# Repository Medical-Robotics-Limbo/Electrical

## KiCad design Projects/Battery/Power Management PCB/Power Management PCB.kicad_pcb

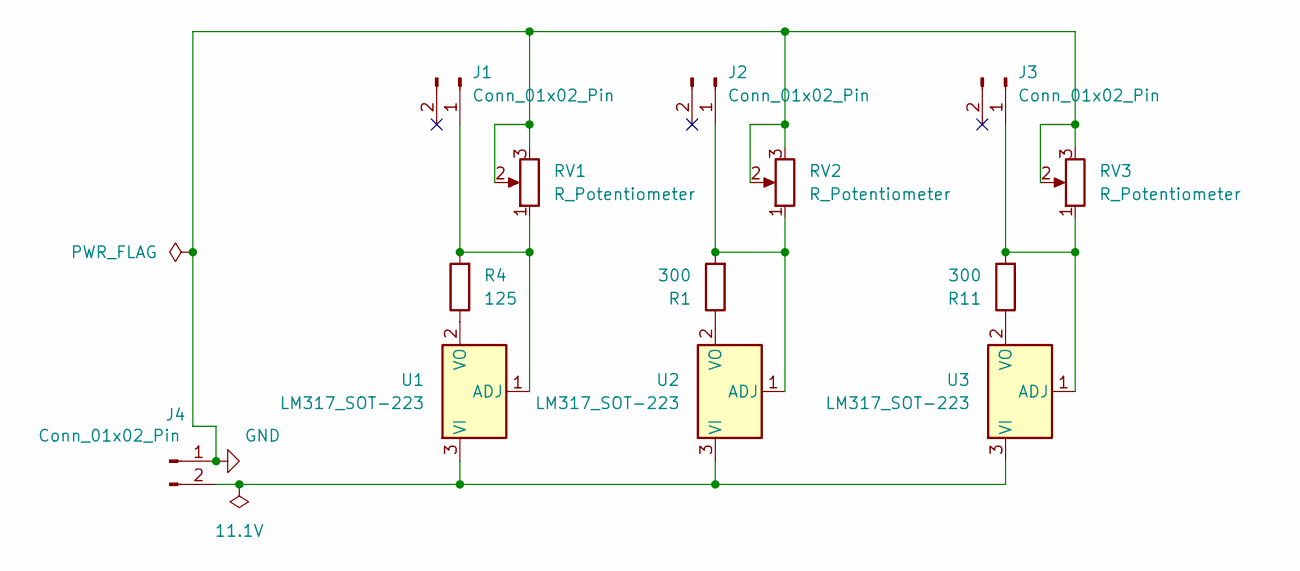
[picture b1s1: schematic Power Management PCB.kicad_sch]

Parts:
J1, J2, J3, J4: Conn_01x02_Pin; PinHeader_1x02_P1.27mm_Vertical_SMD_Pin1Left
R1, R11: 300; R_0201_0603Metric
R4: 125; R_0201_0603Metric
RV1, RV2, RV3: R_Potentiometer; Potentiometer_Bourns_3314J_Vertical
U1, U2, U3: LM317_SOT-223; SOT-223-3_TabPin2

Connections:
GND: J4.1, RV1.2, RV1.3, RV2.2, RV2.3, RV3.2, RV3.3
unnamed: J1.1, R4.2, RV1.1, U1.1 (ADJ)
unnamed: J2.1, R1.2, RV2.1, U2.1 (ADJ)
unnamed: J3.1, R11.2, RV3.1, U3.1 (ADJ)
unnamed: J4.2, U1.3 (VI), U2.3 (VI), U3.3 (VI)
unnamed: R4.1, U1.2 (VO)
unnamed: R1.1, U2.2 (VO)
unnamed: R11.1, U3.2 (VO)

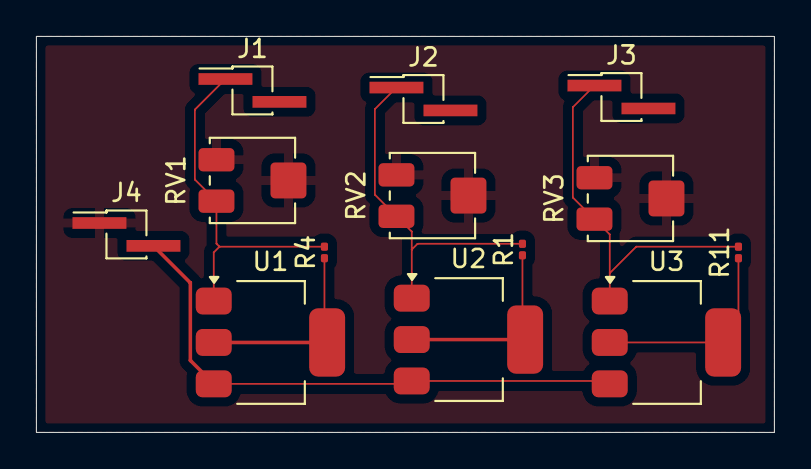
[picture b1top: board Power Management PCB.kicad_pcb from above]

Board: 2 copper layers, 41.0 x 22.0 mm, 13 parts (0 on the bottom side), 8 nets.

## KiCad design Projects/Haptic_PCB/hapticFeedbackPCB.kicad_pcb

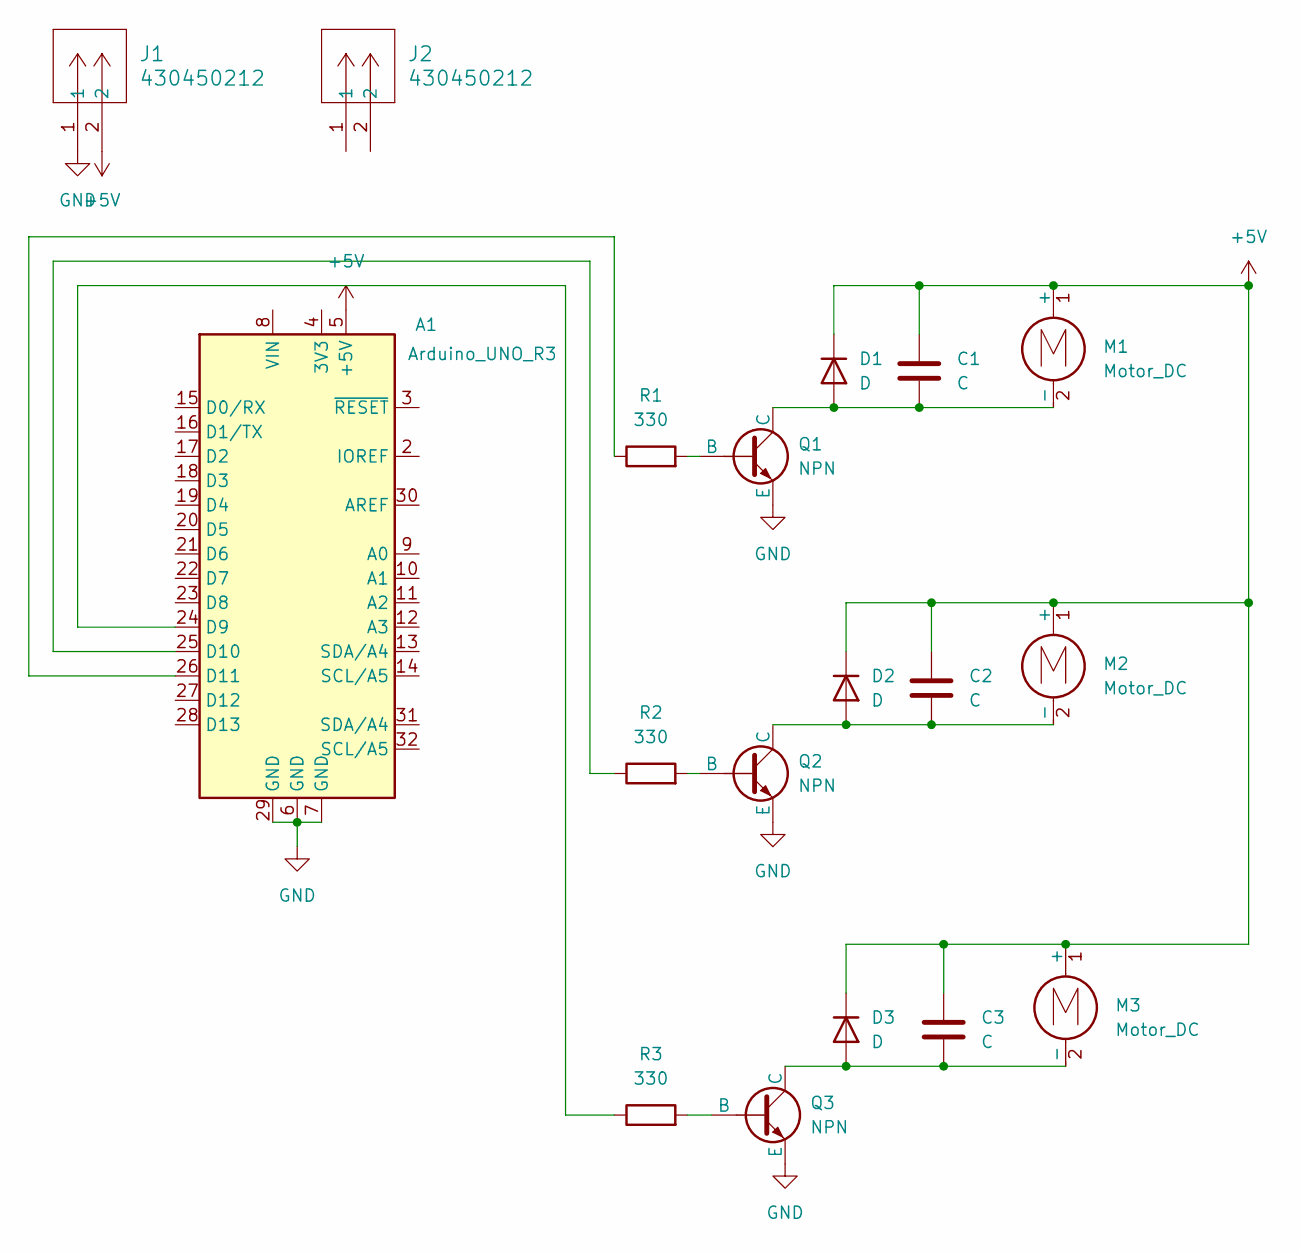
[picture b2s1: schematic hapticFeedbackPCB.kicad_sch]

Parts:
A1: Arduino_UNO_R3
C1, C2, C3: C; CP_Radial_D8.0mm_P5.00mm
D1, D2, D3: D; D_5W_P10.16mm_Horizontal
J1, J2: 430450212; CON_430450212_MOL
M1, M2, M3: Motor_DC; CON_430450212_MOL
Q1, Q2, Q3: NPN; TO-18_TO-206AA_5P8_ONS
R1, R2, R3: 330; R_Axial_DIN0207_L6.3mm_D2.5mm_P10.16mm_Horizontal

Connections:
+5V: A1.5 (+5V), C1.1, C2.1, C3.1, D1.1 (K), D2.1 (K), D3.1 (K), J1.2, M1.1 (+), M2.1 (+), M3.1 (+)
GND: A1.6 (GND), A1.7 (GND), A1.29 (GND), J1.1, Q1.3 (E), Q2.3 (E), Q3.3 (E)
unnamed: A1.24 (D9), R3.1
unnamed: A1.25 (D10), R2.1
unnamed: A1.26 (D11), R1.1
unnamed: C1.2, D1.2 (A), M1.2 (-), Q1.1 (C)
unnamed: C2.2, D2.2 (A), M2.2 (-), Q2.1 (C)
unnamed: C3.2, D3.2 (A), M3.2 (-), Q3.1 (C)
unnamed: Q1.2 (B), R1.2
unnamed: Q2.2 (B), R2.2
unnamed: Q3.2 (B), R3.2

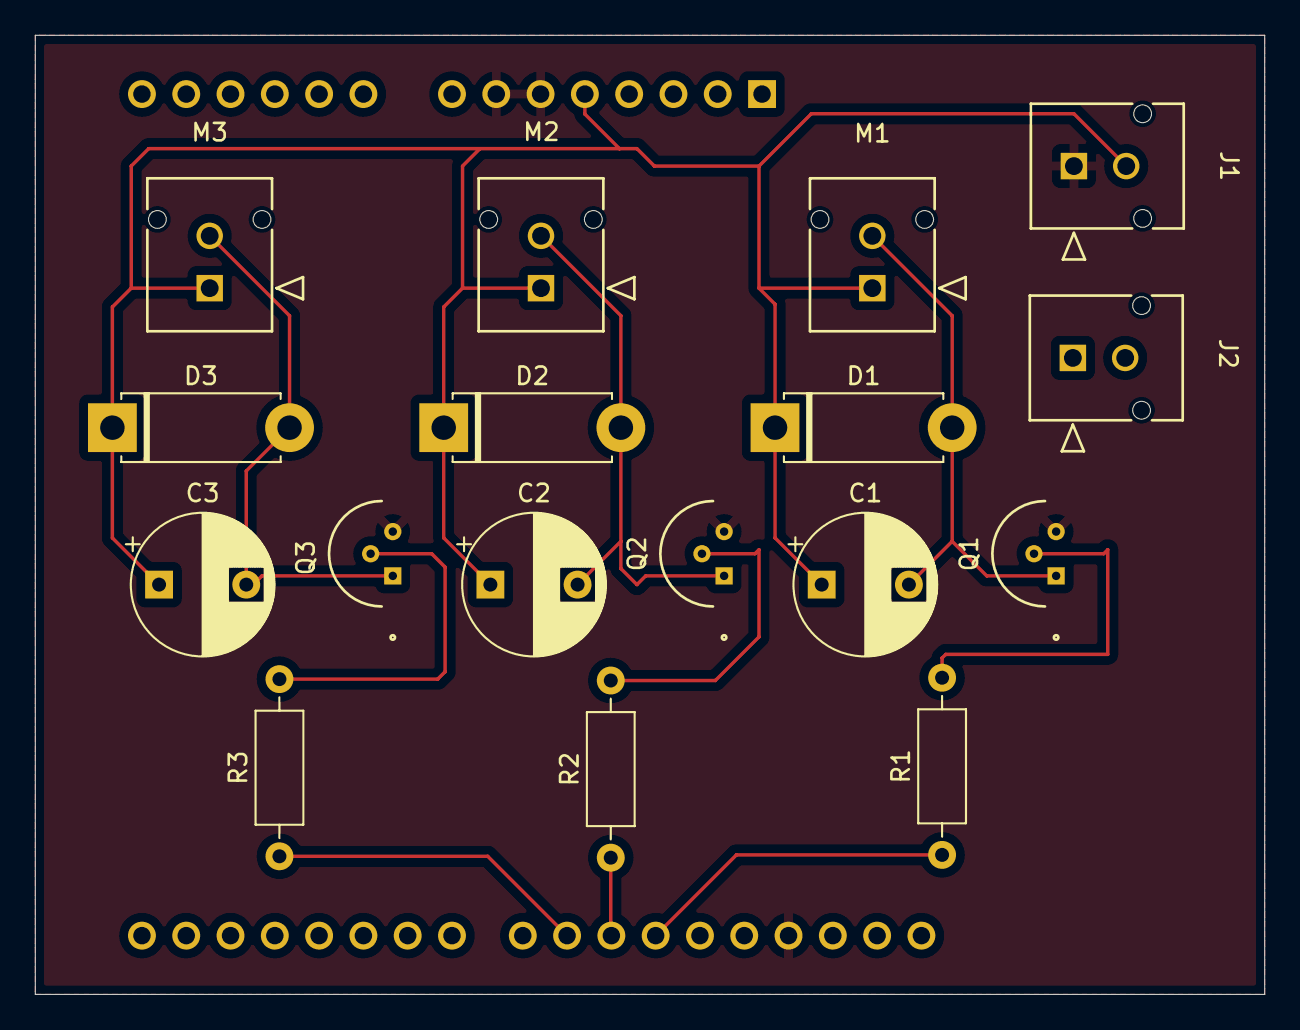
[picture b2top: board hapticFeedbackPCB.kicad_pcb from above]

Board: 2 copper layers, 70.5 x 55.0 mm, 18 parts (1 on the bottom side), 11 nets.

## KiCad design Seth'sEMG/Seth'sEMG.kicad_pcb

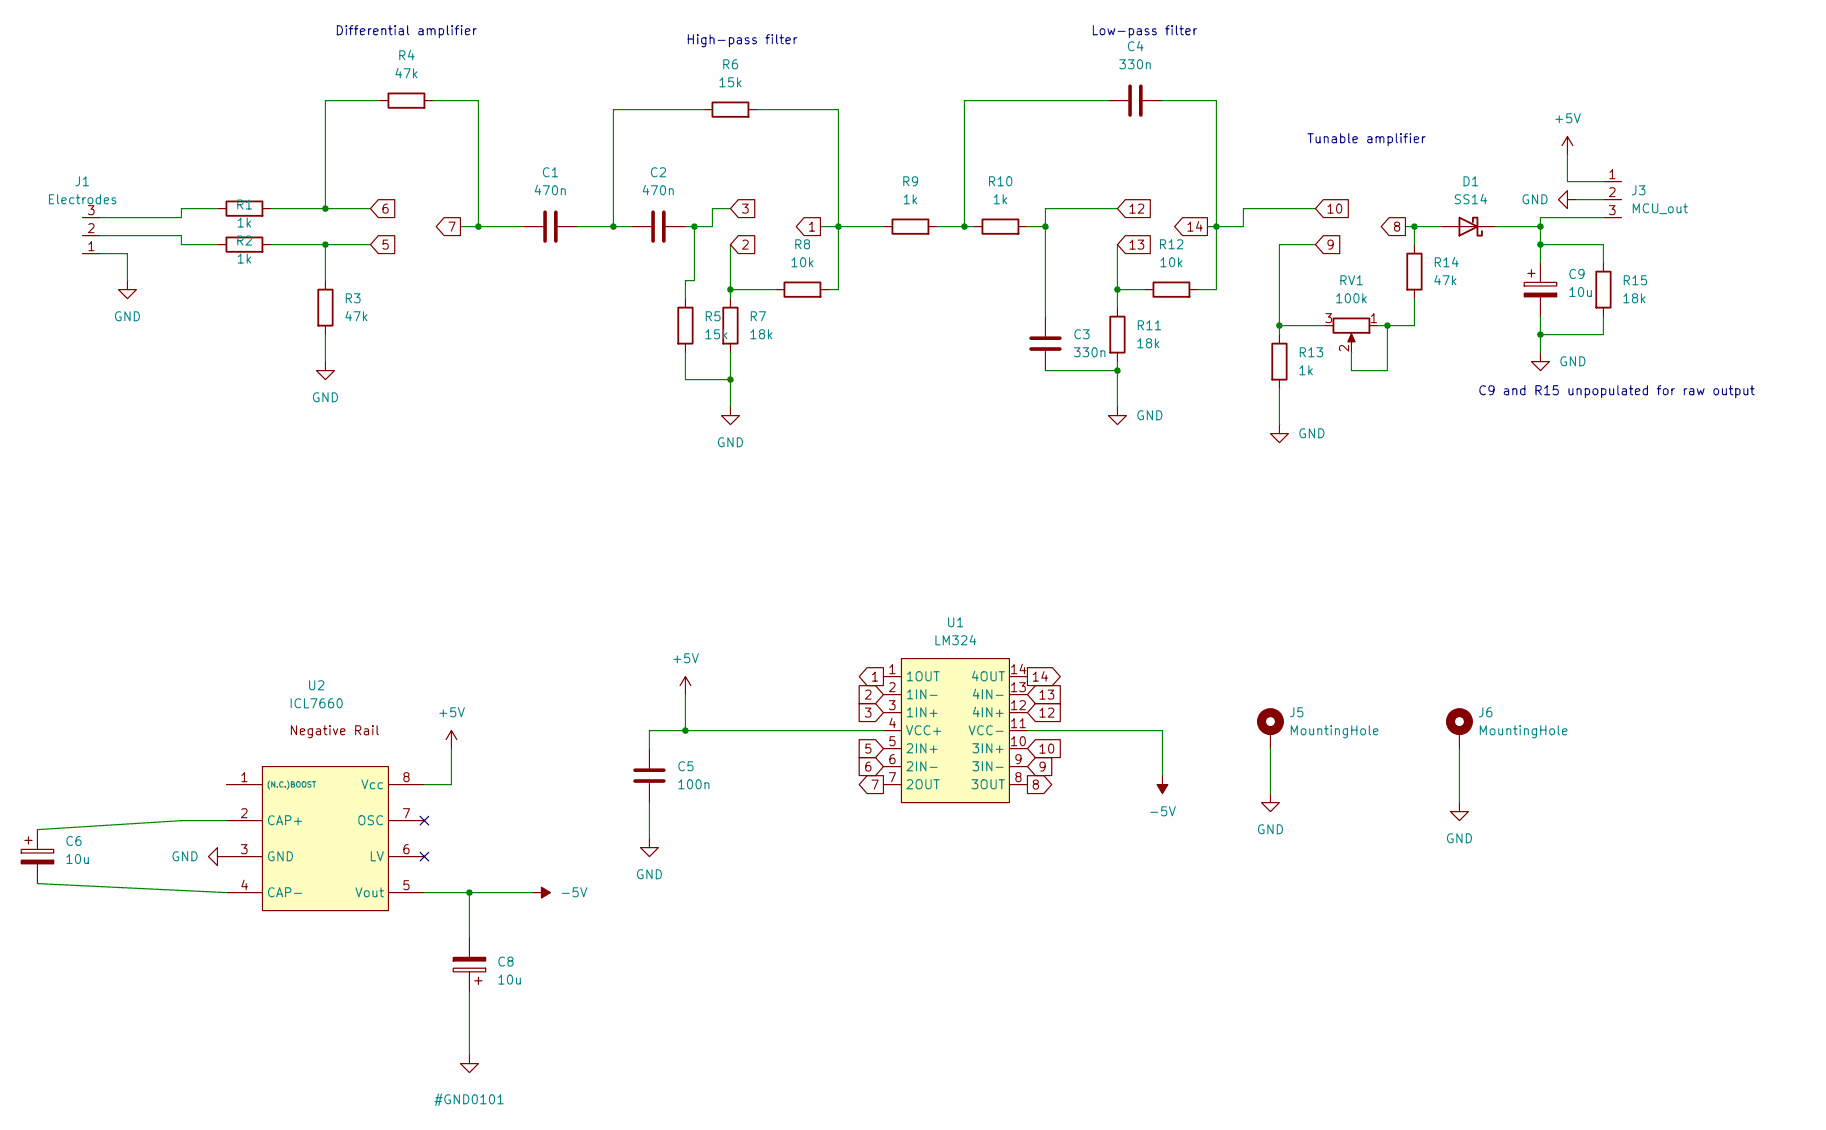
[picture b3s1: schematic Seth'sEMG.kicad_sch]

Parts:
C1, C2: 470n; C_0805_2012Metric
C3, C4: 330n; C_0805_2012Metric
C5: 100n; C_0805_2012Metric
C6, C8, C9: 10u; CP_Elec_6.3x5.4
D1: SS14; D_SMA
J1: Electrodes; PinHeader_1x03_P2.54mm_Vertical
J3: MCU_out; PinHeader_1x03_P2.54mm_Vertical
J5, J6: MountingHole; MountingHole_2.2mm_M2_DIN965_Pad
R1, R2, R9, R10, R13: 1k; R_0805_2012Metric
R3, R4, R14: 47k; R_0805_2012Metric
R5, R6: 15k; R_0805_2012Metric
R7, R11, R15: 18k; R_0805_2012Metric
R8, R12: 10k; R_0805_2012Metric
RV1: 100k; Potentiometer_Bourns_TC33X_Vertical
U1: LM324; SOIC127P600X175-14N
U2: ICL7660; SOIC-8_3.9x4.9mm_P1.27mm

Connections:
1: R6.2, R8.2, R9.1, U1.1 (1OUT)
2: R7.1, R8.1, U1.2 (1IN-)
3: C2.2, R5.1, U1.3 (1IN+)
5: R2.2, R3.1, U1.5 (2IN+)
6: R1.2, R4.1, U1.6 (2IN-)
7: C1.1, R4.2, U1.7 (2OUT)
8: D1.2 (A), R14.1, U1.8 (3OUT)
9: R13.1, RV1.3, U1.9 (3IN-)
10: C4.1, R12.2, U1.10 (3IN+), U1.14 (4OUT)
12: C3.2, R10.2, U1.12 (4IN+)
13: R11.1, R12.1, U1.13 (4IN-)
+5V: C5.1, J3.1, U1.4 (VCC+), U2.8 (Vcc)
-5V: C8.2, U1.11 (VCC-), U2.5 (Vout)
GND: C3.1, C5.2, C8.1, C9.2, J1.1, J3.2, J5.1, J6.1, R3.2, R5.2, R7.2, R11.2, R13.2, R15.2, U2.3 (GND)
unnamed: C1.2, C2.1, R6.1
unnamed: C4.2, R9.2, R10.1
unnamed: C6.1, U2.2 (CAP+)
unnamed: C6.2, U2.4 (CAP-)
unnamed: C9.1, D1.1 (K), J3.3, R15.1
unnamed: J1.2, R2.1
unnamed: J1.3, R1.1
unnamed: R14.2, RV1.1, RV1.2

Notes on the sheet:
Differential amplifier
C9 and R15 unpopulated for raw output
Tunable amplifier
High-pass filter
Low-pass filter

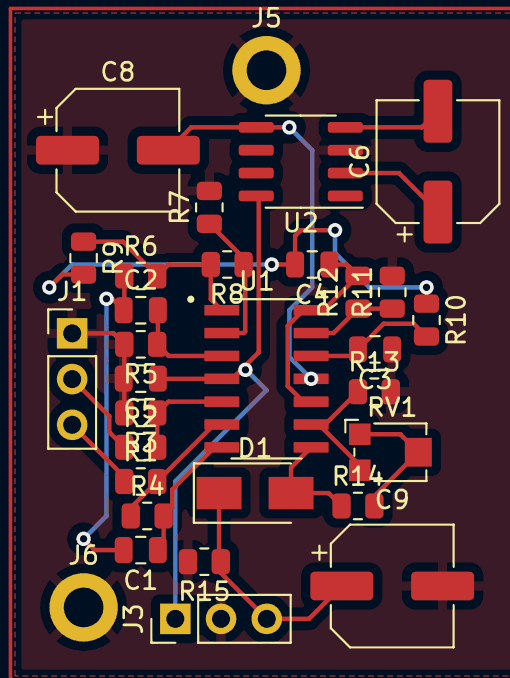
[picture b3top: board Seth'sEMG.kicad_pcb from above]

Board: 2 copper layers, 31 parts (0 on the bottom side), 22 nets.

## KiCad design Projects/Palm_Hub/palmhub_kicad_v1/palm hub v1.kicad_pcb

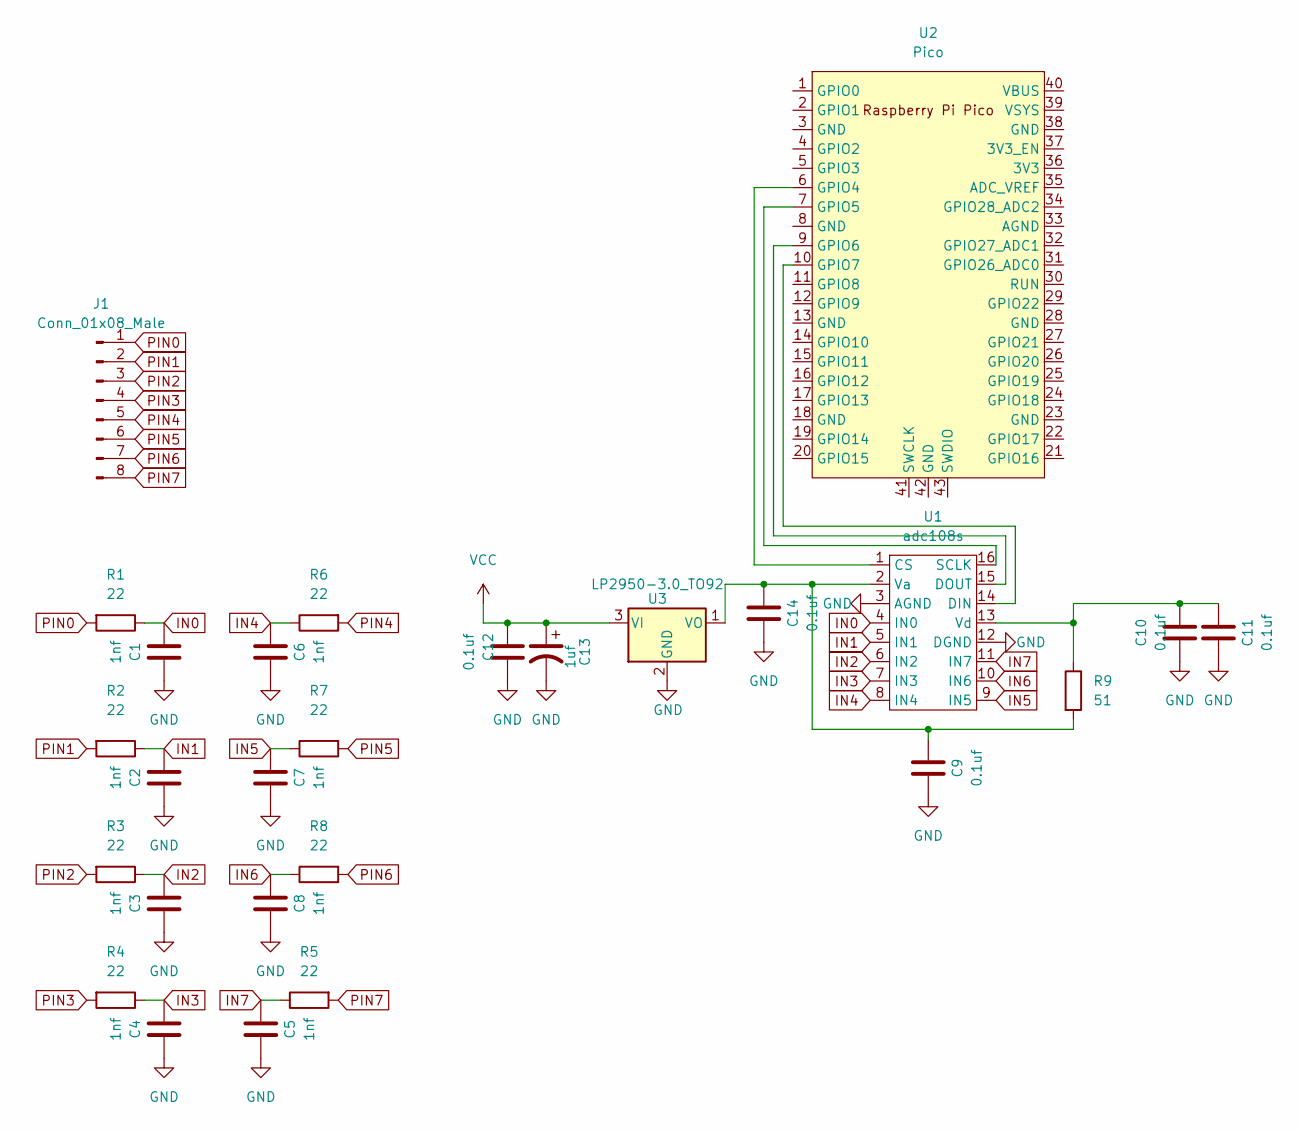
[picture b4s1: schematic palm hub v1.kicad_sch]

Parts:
C1, C2, C3, C4, C5, C6, C7, C8: 1nf; C_0603_1608Metric_Pad1.08x0.95mm_HandSolder
C9, C10, C11, C14: 0.1uf; C_0603_1608Metric_Pad1.08x0.95mm_HandSolder
C12: 1uf; C_0603_1608Metric_Pad1.08x0.95mm_HandSolder
C13: 0.1uf; CP_Radial_D5.0mm_P2.50mm
J1: Conn_01x08_Male; PinHeader_1x08_P2.54mm_Vertical
R1, R2, R3, R4, R5, R6, R7, R8: 22; R_0603_1608Metric_Pad0.98x0.95mm_HandSolder
R9: 51; R_0603_1608Metric_Pad0.98x0.95mm_HandSolder
U1: adc108s; HTSSOP-16-1EP_4.4x5mm_P0.65mm_EP3.4x5mm
U2: Pico; RPi_Pico_SMD_TH
U3: LP2950-3.0_TO92; TO-92_Inline

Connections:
GND: C1.2, C2.2, C3.2, C4.2, C5.2, C6.2, C7.2, C8.2, C9.1, C10.2, C11.2, C12.2, C13.2, C14.1, U1.3 (AGND), U1.12 (DGND), U3.2 (GND); also elsewhere on the board
IN0: C1.1, R1.1, U1.4 (IN0); also elsewhere on the board
IN1: C2.1, R2.1, U1.5 (IN1); also elsewhere on the board
IN2: C3.1, R3.1, U1.6 (IN2); also elsewhere on the board
IN3: C4.1, R4.1, U1.7 (IN3); also elsewhere on the board
IN4: C6.1, R6.1, U1.8 (IN4); also elsewhere on the board
IN5: C7.1, R7.1, U1.9 (IN5); also elsewhere on the board
IN6: C8.1, R8.1, U1.10 (IN6); also elsewhere on the board
IN7: C5.1, R5.1, U1.11 (IN7); also elsewhere on the board
unnamed 9: C10.1, C11.1, R9.1, U1.13 (Vd); also elsewhere on the board
unnamed 10: C9.2, C14.2, R9.2, U1.2 (Va), U3.1 (VO); also elsewhere on the board
unnamed 11: U1.1 (CS), U2.6 (GPIO4); also elsewhere on the board
unnamed 12: U1.14 (DIN), U2.10 (GPIO7); also elsewhere on the board
unnamed 13: U1.15 (DOUT), U2.9 (GPIO6); also elsewhere on the board
unnamed 14: U1.16 (SCLK), U2.7 (GPIO5); also elsewhere on the board
PIN0: J1.1, R1.2
PIN1: J1.2, R2.2
PIN2: J1.3, R3.2
PIN3: J1.4, R4.2
PIN4: J1.5, R6.2
PIN5: J1.6, R7.2
PIN6: J1.7, R8.2
PIN7: J1.8, R5.2
VCC: C12.1, C13.1, U3.3 (VI)

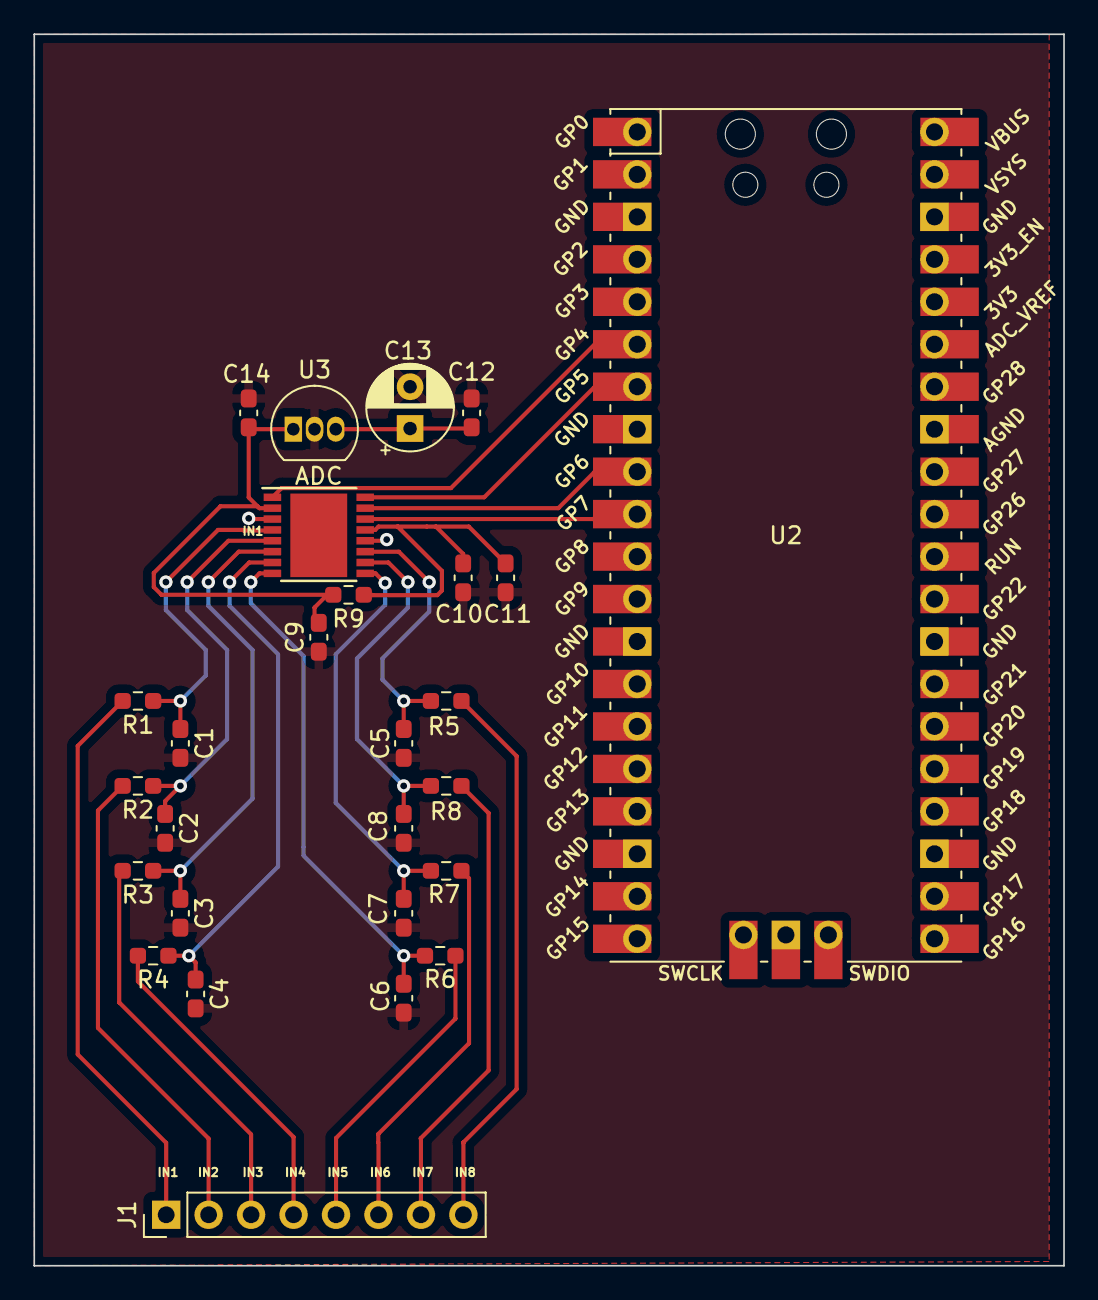
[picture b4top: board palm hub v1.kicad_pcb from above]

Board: 2 copper layers, 61.6 x 73.7 mm, 27 parts (0 on the bottom side), 24 nets.

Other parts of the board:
ADC: adc108s; HTSSOP-16-1EP_4.4x5mm_P0.65mm_EP3.4x5mm

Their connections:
GND: ADC.3 (AGND), ADC.12 (DGND); also elsewhere on the board
IN0: ADC.4 (IN0); also elsewhere on the board
IN1: ADC.5 (IN1); also elsewhere on the board
IN2: ADC.6 (IN2); also elsewhere on the board
IN3: ADC.7 (IN3); also elsewhere on the board
IN4: ADC.8 (IN4); also elsewhere on the board
IN5: ADC.9 (IN5); also elsewhere on the board
IN6: ADC.10 (IN6); also elsewhere on the board
IN7: ADC.11 (IN7); also elsewhere on the board
unnamed 9: ADC.13 (Vd); also elsewhere on the board
unnamed 10: ADC.2 (Va); also elsewhere on the board
unnamed 11: ADC.1 (CS); also elsewhere on the board
unnamed 12: ADC.14 (DIN); also elsewhere on the board
unnamed 13: ADC.15 (DOUT); also elsewhere on the board
unnamed 14: ADC.16 (SCLK); also elsewhere on the board

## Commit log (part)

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2021-12-27 Transferred all files from gatech GitHub
2022-02-12 Fixed PAT9125EL footprint
2022-02-12 Created git ignore for eagle files
2022-02-17 Added multiplexer library
2022-02-21 Added MCU research excel sheet
2022-02-22 changed function names multiplexor
2022-02-22 minor changes
2022-02-24 signal acquisition with amplification LTSpice
2022-02-24 changed signal acquisition opamp
2022-02-24 Reorganized EMG sensor folders into distinct stages
2022-02-24 Auto stash before revert of "Reorganized EMG sensor folders into distinct stages"
2022-02-24 Rebased
2022-02-24 Separated EMG folders
2022-02-24 Added git ignore for LTSpice and MacOS files
2022-03-01 created ADC parts sheet
2022-03-03 Added Mac symlink gen
2022-03-04 Added code to make slip sensor throw error if not connected on setup
2022-03-08 added eagle libraries documentation
2022-03-08 added breakout board schematic for pat9125 slip sensor
2022-03-08 added fsr to eagle libraries
2022-03-10 added RP2040 IC symbol/footprint
2022-03-13 Added FSR resistor calculator
2022-03-15 The changes I made to the PAT9125 breakout board.
2022-03-15 finalized PAT9125 breakout board for ordering
2022-03-29 minor fixes to slip sensor code
2022-03-30 Added rectification ltspice thang - sharty
2022-03-30 Added rectification ltspice thang
2022-04-06 Transfer palm hub ADC schematic
2022-04-06 Added op amp rectification sir-kit
2022-04-07 Uploaded working PAT9125EL code
2022-04-13 setup pins for ADC108 testing script
2022-04-13 attempt SPI reading from ADC
2022-04-13 fixed SPI function call
2022-04-17 Updated rectification circuit
2022-04-21 Update tested ADC SPI data transfer
2022-09-26 Update palm hub test code - separate channel input from data transfer
2022-10-03 Add files via upload
    Code to test controlling the intensity of vibrations from the vibration motor. Includes functions for various pulses.
2022-11-02 Added Potentiometer Position sensing code
2022-11-02 uploaded pico slip sensor test
2022-11-02 Update pot test to include motor feedback loop
    Not yet working, only saves initial pot values
2022-11-14 Create palmhub_KiCad_Naveen (v1)
2022-11-15 Motor Controll Added
2022-12-01 Update Pot Code
2023-02-20 New slipsensor folder
    PAT files are moved to the slipsensor folder and the two slipsensor files are seperated to different folders
2023-03-02 Arduino update serial plotter
    New code on arduino allows to plot the magnitude.
2023-03-08 Code Resets dx and dy to 0
    When there is no shear force, the code resets dx and dy to 0.
2023-03-29 Added seperate file for motor controller testing
2023-04-17 Added single finger motor control to wait for EMG
2023-04-17 Added motor control code for emg side
2023-05-08 WIP: Motor w/ built in Encoder
2023-09-18 Added Seth's EMG PCB work
2023-09-20 Add ADC interrupt code
2023-09-20 Add I2C helper write/read functions
2023-09-20 Add BioTac Product Manual
    electrical schematics and other very important information.
2023-10-04 Testing encoder
2023-10-25 Testing board issues
2023-11-28 PWM control, pid
2024-03-27 new schematic upload
2024-09-18 Added initial files
2024-09-18 Added some footprints
2024-09-23 Added footprints for molex connectors
2024-09-23 Added all footprints
2024-09-25 Added imported footprints and symbols to the project folder
2024-09-26 Created preliminary PCB layout
2024-09-30 Added PCB traces.
2024-10-01 Generated Gerber Files and Drill File
2024-10-21 Create MedRobo_EncoderTest1.ino
    Arduino sketch for encoder version 1
2025-02-18 Test
    Testing whether Github can recognize my changes
2025-02-18 Added Arduino Code and removed test
2025-03-26 Update schematic and layout
2025-09-22 9/22 pcb
